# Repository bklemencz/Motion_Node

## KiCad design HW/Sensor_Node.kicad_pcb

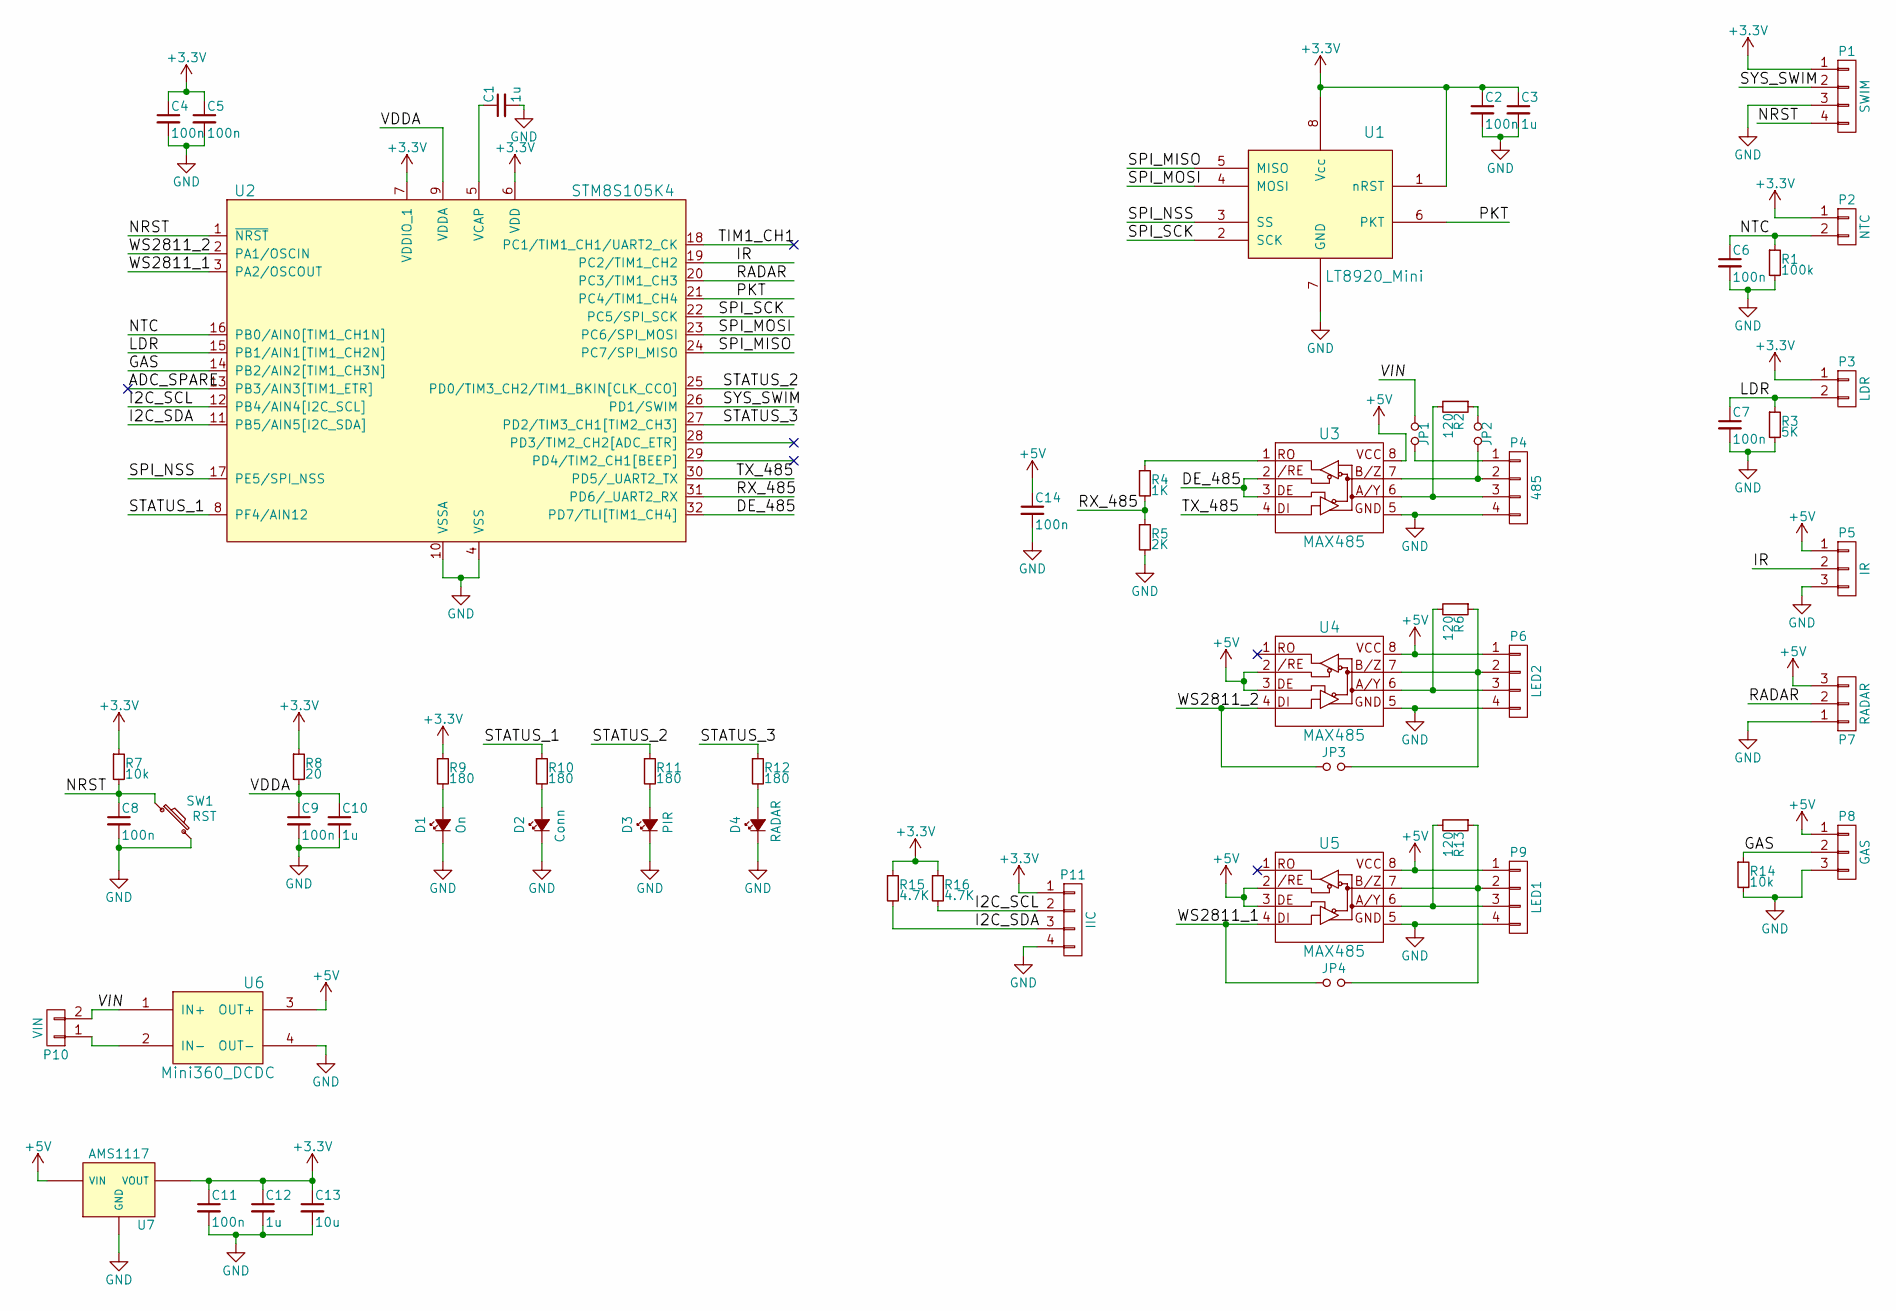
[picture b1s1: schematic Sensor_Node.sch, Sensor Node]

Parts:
C1, C3, C10, C12: 1u; C_0805
C2, C4, C5, C6, C7, C8, C9, C11, C14: 100n; C_0805
C13: 10u; C_1206
D1: On; LED_0805
D2: Conn; LED_0805
D3: PIR; LED_0805
D4: RADAR; LED_0805
JP1, JP2, JP3, JP4: Jumper_NO_Small; 2_pin_solder_jumper_smd
P1: SWIM; JST_B4B-XH-A
P2: NTC; JST_B2B-XH-A
P3: LDR; LDR_5mm_SM
P4: 485; JST_B4B-XH-A
P5: IR; JST_B3B-XH-A
P6: LED2; JST_B4B-XH-A
P7: RADAR; RCWL-0516_3Pin
P8: GAS; JST_B3B-XH-A
P9: LED1; JST_B4B-XH-A
P10: VIN; JST_B2B-XH-A
P11: IIC; Pin_Header_Straight_1x04_Pitch2.54mm
R1: 100k; R_0805
R2, R6, R13: 120; R_0805
R3: 5K; R_0805
R4: 1K; R_0805
R5: 2K; R_0805
R7, R14: 10k; R_0805
R8: 20; R_0805
R9, R10, R11, R12: 180; R_0805
R15, R16: 4.7K; R_0805
SW1: RST; SW_SPST_TACT_SMD_3X6
U1: LT8920_Mini; XY-WB_LT8920
U2: STM8S105K4; LQFP-32_7x7mm_Pitch0.8mm
U3, U4, U5: MAX485; SOIC-8_3.9x4.9mm_Pitch1.27mm
U6: Mini360_DCDC
U7: AMS1117; SOT-223

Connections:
+3V3: C2.1, C3.1, C4.1, C5.1, C11.1, C12.1, C13.1, P1.1, P2.1, P3.1, P11.1, R7.1, R8.1, R9.1, R15.1, R16.1, U1.1 (nRST), U1.8 (Vcc), U2.6 (VDD), U2.7 (VDDIO_1), U7.2 (VOUT)
+5V: C14.1, P5.1, P6.1, P7.3, P8.1, P9.1, U3.8 (VCC), U4.2 (/RE), U4.3 (DE), U4.8 (VCC), U5.2 (/RE), U5.3 (DE), U5.8 (VCC), U6.3 (OUT+), U7.3 (VIN)
/ADC_SPARE: U2.13 (PB3/AIN3[TIM1_ETR])
/DE_485: U2.32 (PD7/TLI[TIM1_CH4]), U3.2 (/RE), U3.3 (DE)
/GAS: P8.2, R14.1, U2.14 (PB2/AIN2[TIM1_CH3N])
/I2C_SCL: P11.2, R16.2, U2.12 (PB4/AIN4[I2C_SCL])
/I2C_SDA: P11.3, R15.2, U2.11 (PB5/AIN5[I2C_SDA])
/IR: P5.2, U2.19 (PC2/TIM1_CH2)
/LDR: C7.1, P3.2, R3.1, U2.15 (PB1/AIN1[TIM1_CH2N])
/NRST: C8.1, P1.4, R7.2, SW1.1, U2.1 (~NRST)
/NTC: C6.1, P2.2, R1.1, U2.16 (PB0/AIN0[TIM1_CH1N])
/PKT: U1.6 (PKT), U2.21 (PC4/TIM1_CH4)
/RADAR: P7.2, U2.20 (PC3/TIM1_CH3)
/RX_485: R4.2, R5.1, U2.31 (PD6/_UART2_RX)
/SPI_MISO: U1.5 (MISO), U2.24 (PC7/SPI_MISO)
/SPI_MOSI: U1.4 (MOSI), U2.23 (PC6/SPI_MOSI)
/SPI_NSS: U1.3 (SS), U2.17 (PE5/SPI_NSS)
/SPI_SCK: U1.2 (SCK), U2.22 (PC5/SPI_SCK)
/STATUS_1: R10.1, U2.8 (PF4/AIN12)
/STATUS_2: R11.1, U2.25 (PD0/TIM3_CH2/TIM1_BKIN[CLK_CCO])
/STATUS_3: R12.1, U2.27 (PD2/TIM3_CH1[TIM2_CH3])
/SYS_SWIM: P1.2, U2.26 (PD1/SWIM)
/TIM1_CH1: U2.18 (PC1/TIM1_CH1/UART2_CK)
/TX_485: U2.30 (PD5/_UART2_TX), U3.4 (DI)
/VDDA: C9.1, C10.1, R8.2, U2.9 (VDDA)
/VIN: JP1.1, P10.2, U6.1 (IN+)
/WS2811_1: JP4.1, U2.3 (PA2/OSCOUT), U5.4 (DI)
/WS2811_2: JP3.1, U2.2 (PA1/OSCIN), U4.4 (DI)
GND: C1.2, C2.2, C3.2, C4.2, C5.2, C6.2, C7.2, C8.2, C9.2, C10.2, C11.2, C12.2, C13.2, C14.2, D1.1 (K), D2.1 (K), D3.1 (K), D4.1 (K), P1.3, P4.4, P5.3, P6.4, P7.1, P8.3, P9.4, P11.4, R1.2, R3.2, R5.2, R14.2, SW1.2, U1.7 (GND), U2.4 (VSS), U2.10 (VSSA), U3.5 (GND), U4.5 (GND), U5.5 (GND), U6.4 (OUT-), U7.1 (GND)
unnamed: C1.1, U2.5 (VCAP)
unnamed: D1.2 (A), R9.2
unnamed: D2.2 (A), R10.2
unnamed: D3.2 (A), R11.2
unnamed: D4.2 (A), R12.2
unnamed: JP1.2, P4.1
unnamed: JP2.1, R2.1
unnamed: JP2.2, P4.2, U3.7 (B/Z)
unnamed: JP3.2, P6.2, R6.1, U4.7 (B/Z)
unnamed: JP4.2, P9.2, R13.1, U5.7 (B/Z)
unnamed: P4.3, R2.2, U3.6 (A/Y)
unnamed: P6.3, R6.2, U4.6 (A/Y)
unnamed: P9.3, R13.2, U5.6 (A/Y)
unnamed: P10.1, U6.2 (IN-)
unnamed: R4.1, U3.1 (RO)

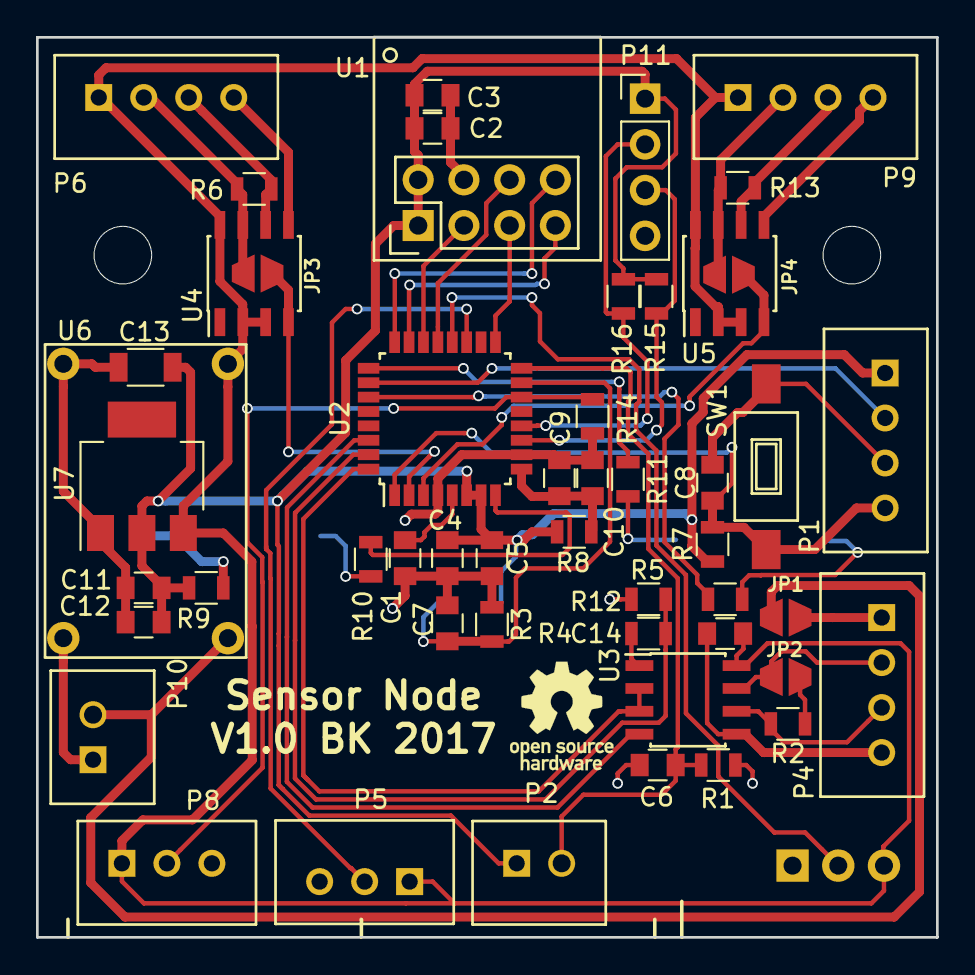
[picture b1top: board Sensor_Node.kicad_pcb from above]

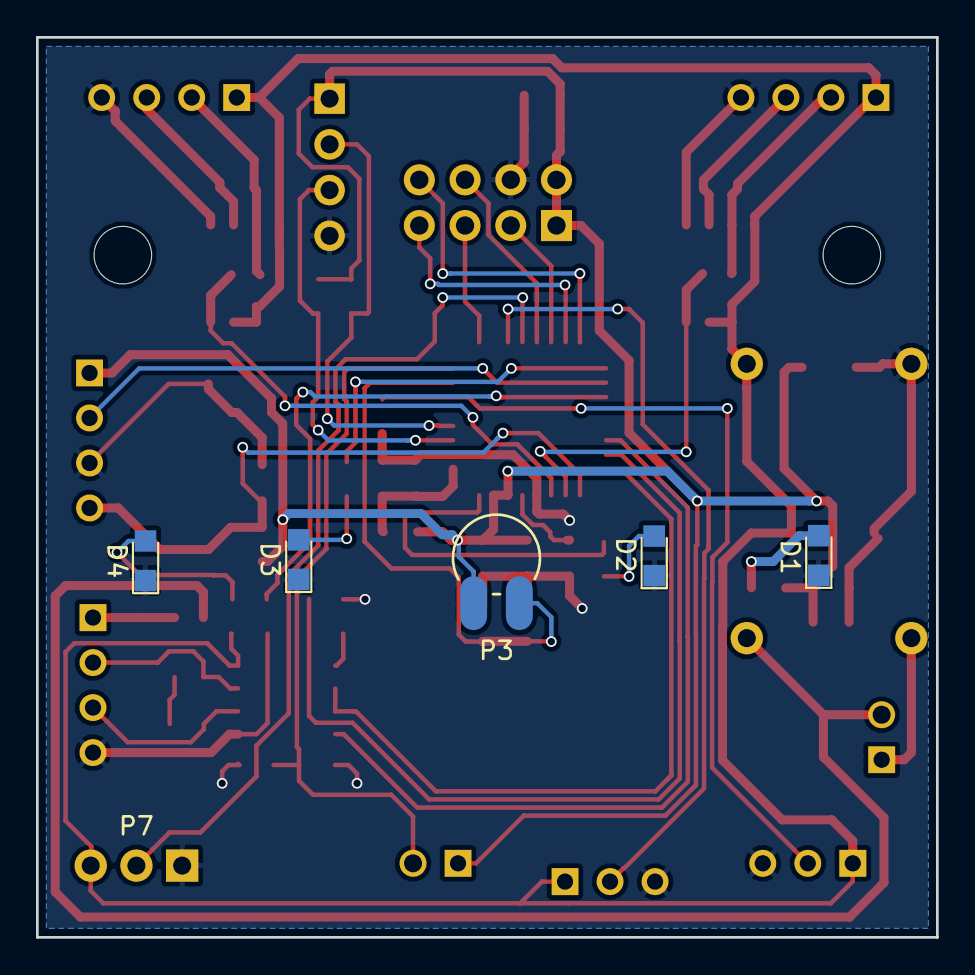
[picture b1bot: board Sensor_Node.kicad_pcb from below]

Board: 2 copper layers, 50.0 x 50.0 mm, 57 parts (6 on the bottom side), 42 nets.

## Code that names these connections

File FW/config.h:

/*
Dec 10 2020 V2.11 
CHANGE
 - Sequence check on RF commands to filter multiples
 - Lt8900 reset if corrupted
 - Shutter working
 - Broadcast ID at commands
 - Rx Mode immedeiately after send

Dec 15 2020 V2.12 
 - Command 10 to set periodic message timer
 - Create command spreadsheet
 - Multiple message sending
 - Commands update as in spreadsheet

 TODO
 
 - Turn off when hold
 - Motion enabled on single press
 - Add Temp calib 
 - Add light level calib

*/
#ifndef __CONFIG_H
#define __CONFIG_H

#include "inc\stm8s.h"
#include "inc\stm8s_adc1.h"
#include "inc\stm8s_exti.h"
#include "inc\stm8s_gpio.h"
#include "inc\stm8s_i2c.h"
#include "inc\stm8s_spi.h"
#include "inc\stm8s_tim1.h"
#include "inc\stm8s_tim2.h"
#include "inc\stm8s_tim3.h"
#include "inc\stm8s_tim4.h"
#include "inc\stm8s_uart2.h"
#include "inc\stm8s_clk.h"
#include "delay.h"
#include "math.h"



#define RF_COM_USE              1
#define RF_NODEID_DEF           0x12
#define RF_MILIGHT_REMOTE       1
#define RF_MILIGHT_GATEW        1
#define RF_MILIGHT_HOLD_STEP    5
#define RF_TX_PERIODIC_SEND     1
#define RF_TX_PERIODIC_TIME     30000
#define RF_TX_REPEAT            4

#define LIGHTS_BY_MOTION        1
#define START_LEDON             1
#define LIGHTS_OFF_DELAY_S      10
#define LIGHT_MAX_PERCENT       99
#define LIGHT_NIGHT_PERCENT     10
#define RF_MI_LEARN_WINDOW_MS   60000
#define LED_FADE_ENABLED        1
#define LED_FADE_DELAY_MS       10
#define LED_RX_FADE_DELAY_EN    1
#define LED_DELAY_AFTER_RX      350
#define LED_FLASH_BRIGHTNESS    30

#define AD_HAS_NTC              1
#define AD_HAS_LDR              1
#define AD_HAS_GAS_SENSOR       1
#define AD_CAPT_DELAY_MS        5000
#define AD_AVG_COUNT            10
#define AD_MAX_LOOKUP_SIZE      21

#define HAS_PIR                 1
#define HAS_RADAR               1
#define PIR_DELAY_MS            380
#define RADAR_DELAY_MS          380

#define USE_485_COM             1
#define RS485_BAUD              57600
#define RS485_CHAR_DELAY        1
#define RS485_MESSAGE_DELAY     60

#define MAINSTATE_IDLE          0
#define MAINSTATE_AD            1
#define MAINSTATE_WS            2
#define MAINSTATE_RFRX          4
#define MAINSTATE_RFTX          8

#define MAINCONFIG_USERF        0       //USE RF FUCTIONS
#define MAINCONFIG_MIREM        1       //MI REMOTE RECEIVE FUNCTIONS
#define MAINCONFIG_MIGAT        2       //MI REMOTE GATEWAY FUNCTIONS
#define MAINCONFIG_MOVL         3
#define MAINCONFIG_FADEE        4       //LIGHT FADING ENABLED
#define MAINCONFIG_STRTON       5       //START ON WHEN STARTUP
#define MAINCONFIG_FADEDELEN    6       //FADE DELAY for remote hold
#define MAINCONFIG_RFPERTXEN    7       //PERIODIC MESSAGES ENABLED

#define RF_TX_MSG_REQ           0
#define RF_TX_MSG_RES           1
#define RF_TX_MSG_PER           2
#define RF_TX_MSG_ALM           3

#define RF_TX_ARQ               5
#define RF_TX_ARS               4

#define RF_RX_MOT_ALM           16
#define RF_TX_ALM_ITEM          64
#define RF_TX_PER_ITEM          65



#define LT8900_PKT_GPIO_PORT    (GPIOC)
#define LT8900_PKT_PIN          (GPIO_PIN_4)
#define LT8900_NCS_GPIO_PORT		(GPIOE)
#define LT8900_NCS_PIN          (GPIO_PIN_5)
#define SPI_PRESC               SPI_BAUDRATEPRESCALER_16

#define RS485_TXEN_PORT         (GPIOD)
#define RS485_TXEN_PIN          (GPIO_PIN_7)

#define RADAR_GPIO_PORT					(GPIOC)
#define RADAR_PIN								(GPIO_PIN_3)

#define PIR_GPIO_PORT						(GPIOC)
#define PIR_PIN									(GPIO_PIN_2)

#define AD_GPIO_PORT						(GPIOB)

#define NTC_AD_PIN							(GPIO_PIN_0)
#define NTC_AD_CHANNEL					(ADC1_CHANNEL_0)
#define NTC_USE_STEINHART       1
#define NTC_SER_RES             10000
#define NTC_R_NOM               10000
#define NTC_COEFF               3950
#define NTC_T_NOM               25

#define LDR_AD_PIN							(GPIO_PIN_1)
#define LDR_AD_CHANNEL					(ADC1_CHANNEL_1)

#define GAS_AD_PIN							(GPIO_PIN_2)
#define GAS_AD_CHANNEL					(ADC1_CHANNEL_2)

#define ADC_SPARE_AD_PIN				(GPIO_PIN_3)
#define ADC_SPARE_AD_CHANNEL		(ADC1_CHANNEL_3)

#define WS2811_GPIO_PORT				(GPIOA)
#define WS2811_1_PIN						(GPIO_PIN_1)
#define WS2811_2_PIN						(GPIO_PIN_2)
#define WS2811_MAX_CHANNELS			20

#define STATUS_1_GPIO_PORT			(GPIOF)                //Blue Status LED
#define STATUS_1_PIN						(GPIO_PIN_4)        //Blue Status LED
#define STATUS_2_GPIO_PORT			(GPIOD)					
#define STATUS_2_PIN						(GPIO_PIN_0)
#define STATUS_3_GPIO_PORT			(GPIOD)
#define STATUS_3_PIN						(GPIO_PIN_2)



#define TIM4_PERIOD             124
#define TIM4_PRESC              TIM4_PRESCALER_128




#define _BV(bit) (1 << (bit))
#define bitRead(value, bit) (((value) >> (bit)) & 0x01)

#endif

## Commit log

2017-12-04 :tada: Added .gitattributes & .gitignore files
2017-12-04 initial
2017-12-04 PCB Update
2020-12-03 RS485 for PWM boards enabled
2020-12-03 Remove Object files
2020-12-04 Added Shutter Control Function
2020-12-14 v2.11 Command messaging changes
2020-12-16 V 2.12 Commands update
2021-01-28 Command DOC update
